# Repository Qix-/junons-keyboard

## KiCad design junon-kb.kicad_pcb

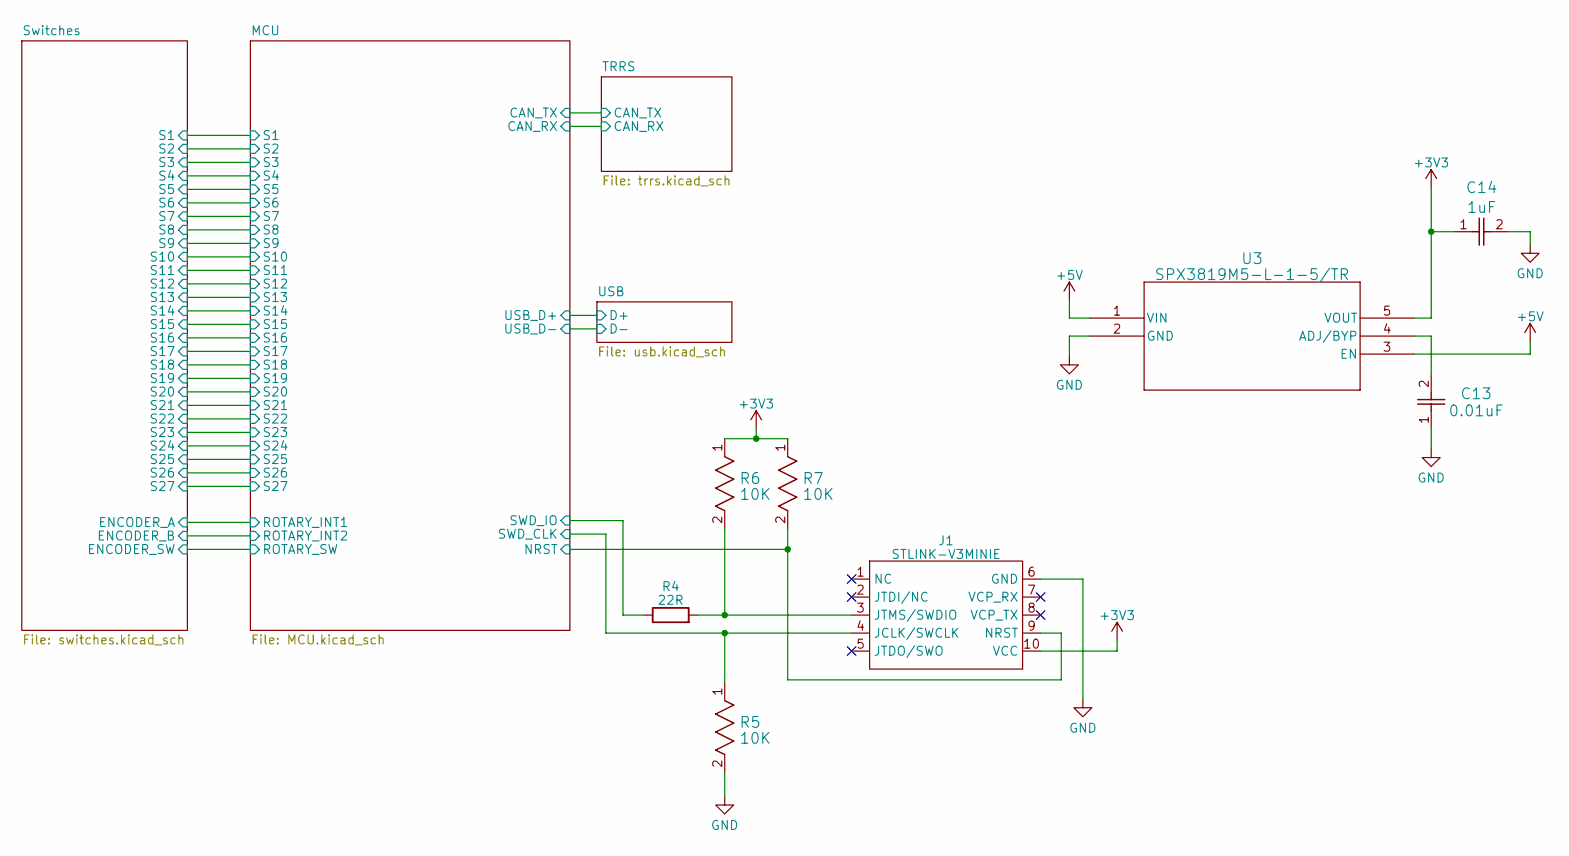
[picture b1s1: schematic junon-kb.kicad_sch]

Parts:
C13: 0.01uF; CAP_CL21_SAM; DigiKey ID 1276-1015-1-ND
C14: 1uF; CAP_0603G_AVX; Mouser ID 581-0603YD105K
J1: STLINK-V3MINIE; 009159010061911; Manufacturer_Part_Number STLINK-V3MINIE; Mouser Part Number 511-STLINK-V3MINIE
R4: 22R; R_01005_0402Metric
R5, R6, R7: 10K; RES_RK73H1E_KOA; Mouser ID 660-RK73H1ETTP1002F
U3: SPX3819M5-L-1-5/TR; SOT-23-5_VAR-AA; Mouser ID 701-SPX3819M5-L-15TR

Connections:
+3V3: C14.1, J1.10 (VCC), R6.1, R7.1, U3.5 (VOUT); also elsewhere on the board
+5V: U3.1 (VIN), U3.3 (EN); also elsewhere on the board
/MCU/NRST: J1.9 (NRST), R7.2; also elsewhere on the board
/MCU/SWD_CLK: J1.4 (JCLK/SWCLK), R5.1; also elsewhere on the board
/MCU/SWD_IO: R4.1; also elsewhere on the board
GND: C13.1, C14.2, J1.6 (GND), R5.2, U3.2 (GND); also elsewhere on the board
unnamed: J1.3 (JTMS/SWDIO), R4.2, R6.2
unnamed: C13.2, U3.4 (ADJ/BYP)

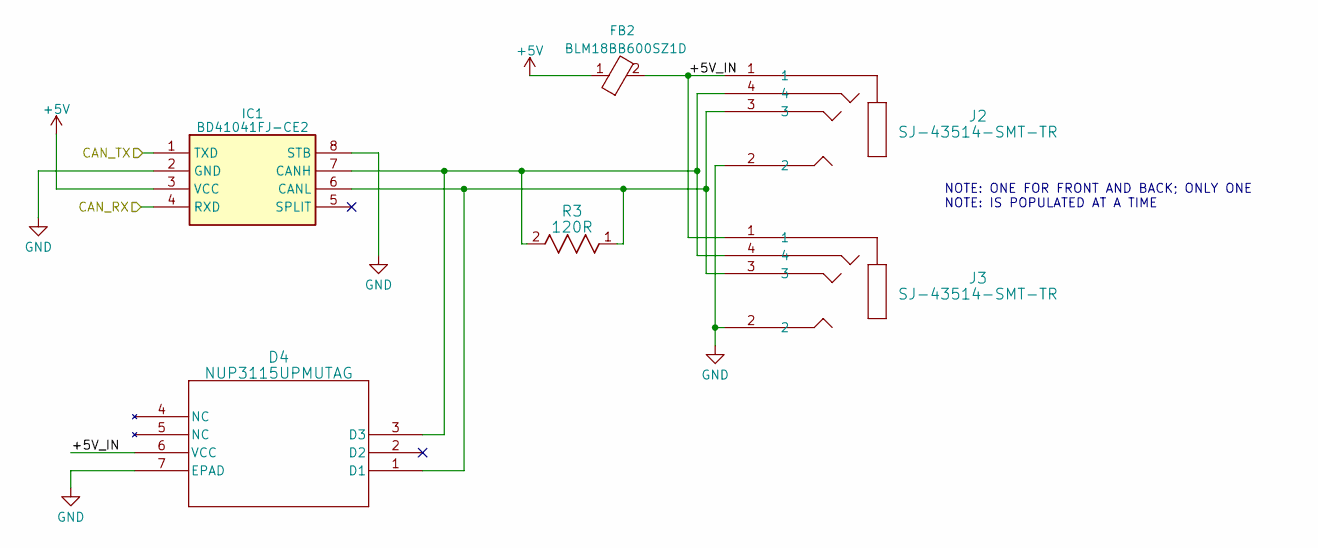
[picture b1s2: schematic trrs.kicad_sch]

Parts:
D4: NUP3115UPMUTAG; UDFN6_1P60X1P60_ONS; Mouser ID 863-NUP3115UPMUTAG
FB2: BLM18BB600SZ1D; BLM18EG121SH1D; Manufacturer_Part_Number BLM18BB600SZ1D; Mouser Part Number 81-BLM18BB600SZ1D
IC1: BD41041FJ-CE2; SOIC127P600X165-8N; Manufacturer_Part_Number BD41041FJ-CE2; Mouser Part Number 755-BD41041FJ-CE2
J2, J3: SJ-43514-SMT-TR; SJ-43514-SMT_CUD; DigiKey ID CP-43514SJCT-ND
R3: 120R; RES_0603_1P6XP8_PAN; Mouser ID 667-ERJ-PA3F1200V

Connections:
+5V: FB2.1, IC1.3 (VCC); also elsewhere on the board
/MCU/CAN_RX: IC1.4 (RXD); also elsewhere on the board
/MCU/CAN_TX: IC1.1 (TXD); also elsewhere on the board
/TRRS/+5V_IN: D4.6 (VCC), FB2.2, J2.1, J3.1
GND: D4.7 (EPAD), IC1.2 (GND), IC1.8 (STB), J2.2, J3.2; also elsewhere on the board
unnamed: D4.1 (D1), IC1.6 (CANL), J2.3, J3.3, R3.1
unnamed: D4.3 (D3), IC1.7 (CANH), J2.4, J3.4, R3.2

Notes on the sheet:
NOTE: ONE FOR FRONT AND BACK; ONLY ONE NOTE: IS POPULATED AT A TIME

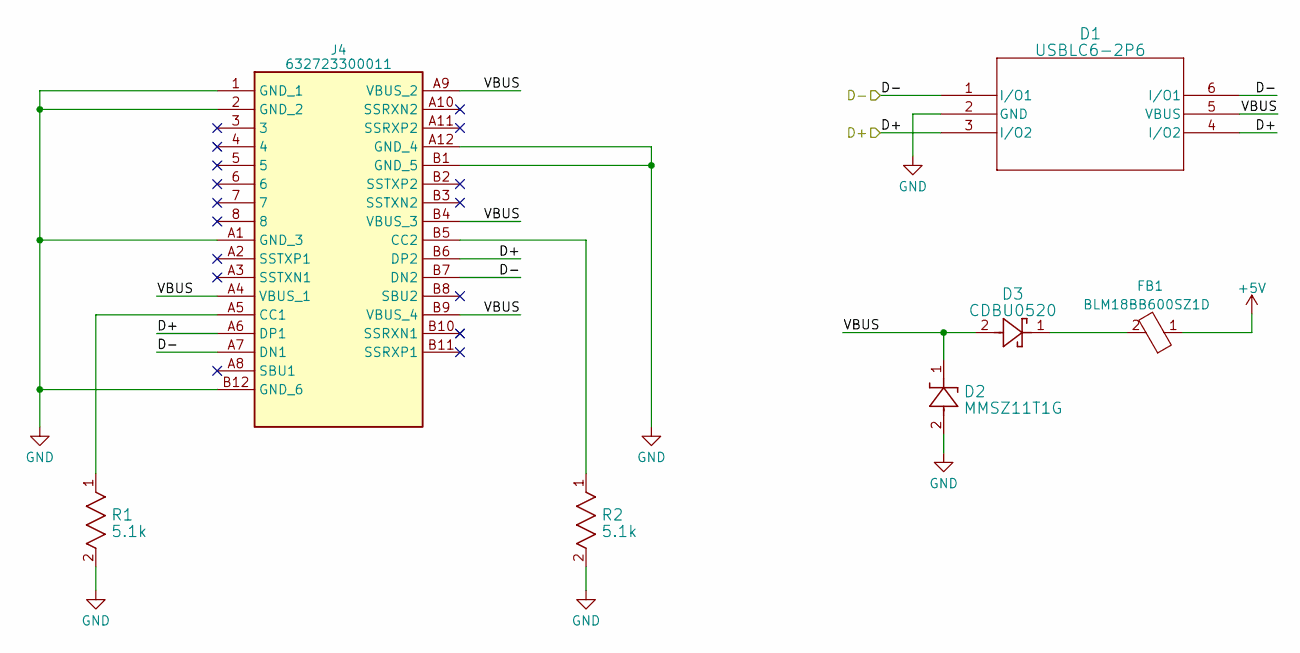
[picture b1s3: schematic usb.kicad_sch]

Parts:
D1: USBLC6-2P6; SOT-666_STM; Mouser ID 511-USBLC6-2P6
D2: MMSZ11T1G; SOD-123_ONS; Mouser ID 863-MMSZ11T1G
D3: CDBU0520; CDBU; Mouser ID 750-CDBU0520
FB1: BLM18BB600SZ1D; BLM18EG121SH1D; Manufacturer_Part_Number BLM18BB600SZ1D; Mouser Part Number 81-BLM18BB600SZ1D
J4: 632723300011; Manufacturer_Part_Number 632723300011; Mouser Part Number 710-632723300011
R1, R2: 5.1k; RES_ERJUP3_PAN; Mouser ID 667-ERJ-UP3F5101V

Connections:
+5V: FB1.1; also elsewhere on the board
/USB/D+: D1.3 (I/O2), D1.4 (I/O2), J4.A6 (DP1), J4.B6 (DP2); also elsewhere on the board
/USB/D-: D1.1 (I/O1), D1.6 (I/O1), J4.A7 (DN1), J4.B7 (DN2); also elsewhere on the board
/USB/VBUS: D1.5 (VBUS), D2.1, D3.2, J4.A4 (VBUS_1), J4.A9 (VBUS_2), J4.B4 (VBUS_3), J4.B9 (VBUS_4)
GND: D1.2 (GND), D2.2, J4.1 (GND_1), J4.2 (GND_2), J4.A1 (GND_3), J4.A12 (GND_4), J4.B1 (GND_5), J4.B12 (GND_6), R1.2, R2.2; also elsewhere on the board
unnamed: D3.1, FB1.2
unnamed: J4.A5 (CC1), R1.1
unnamed: J4.B5 (CC2), R2.1

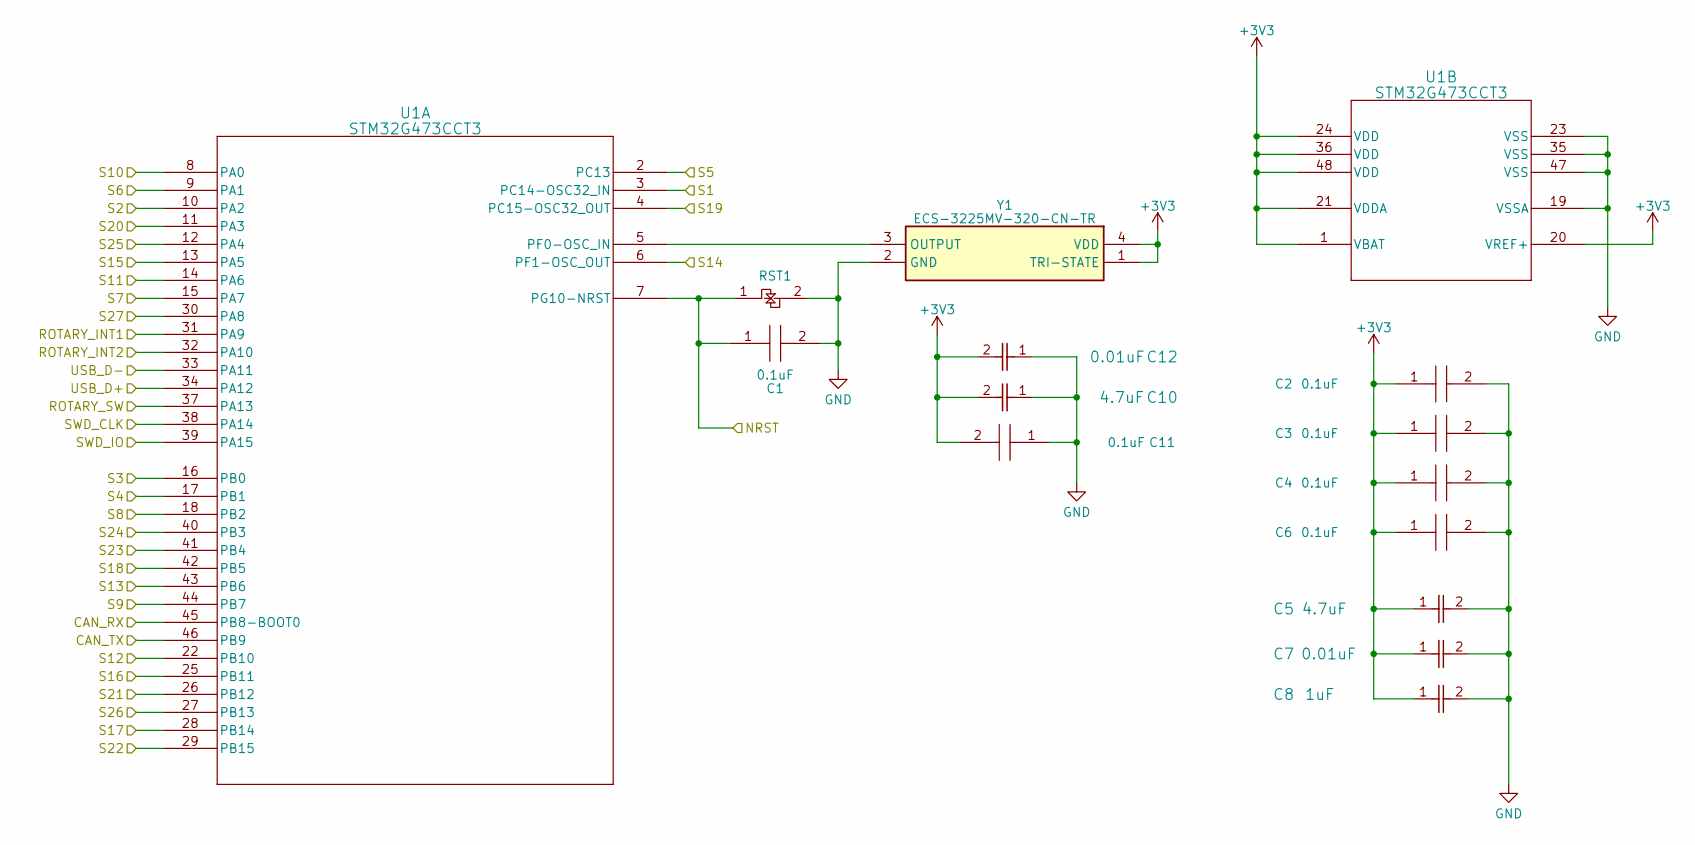
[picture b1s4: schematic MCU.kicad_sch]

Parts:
C1, C2, C3, C4, C6, C11: 0.1uF; CAPC1005X33N; Manufacturer_Part_Number MSAST1L3YB5104KFNA01; Mouser Part Number 963-MSAST1L3YB5104KF
C5, C10: 4.7uF; CAP_CL21_SAM; Mouser URL null
C7, C12: 0.01uF; CAP_CL21_SAM; DigiKey ID 1276-1015-1-ND
C8: 1uF; CAP_0603G_AVX; Mouser ID 581-0603YD105K
RST1: RESET-2P-EDGE
U1: STM32G473CCT3; LQFP48-7x7mm; Mouser ID 511-STM32G473CCT3
Y1: ECS-3225MV-320-CN-TR; ECS3225MV320BNTR; Manufacturer_Part_Number ECS-3225MV-320-CN-TR; Mouser Part Number 520-3225MV-320-CNT

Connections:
+3V3: C2.1, C3.1, C4.1, C5.1, C6.1, C7.1, C8.1, C10.2, C11.2, C12.2, U1.1 (VBAT), U1.20 (VREF+), U1.21 (VDDA), U1.24 (VDD), U1.36 (VDD), U1.48 (VDD), Y1.1 (TRI-STATE), Y1.4 (VDD); also elsewhere on the board
/MCU/CAN_RX: U1.45 (PB8-BOOT0); also elsewhere on the board
/MCU/CAN_TX: U1.46 (PB9); also elsewhere on the board
/MCU/NRST: C1.1, RST1.1, U1.7 (PG10-NRST); also elsewhere on the board
/MCU/ROTARY_INT1: U1.31 (PA9); also elsewhere on the board
/MCU/ROTARY_INT2: U1.32 (PA10); also elsewhere on the board
/MCU/ROTARY_SW: U1.37 (PA13); also elsewhere on the board
/MCU/S1: U1.3 (PC14-OSC32_IN); also elsewhere on the board
/MCU/S2: U1.10 (PA2); also elsewhere on the board
/MCU/S3: U1.16 (PB0); also elsewhere on the board
/MCU/S4: U1.17 (PB1); also elsewhere on the board
/MCU/S5: U1.2 (PC13); also elsewhere on the board
/MCU/S6: U1.9 (PA1); also elsewhere on the board
/MCU/S7: U1.15 (PA7); also elsewhere on the board
/MCU/S8: U1.18 (PB2); also elsewhere on the board
/MCU/S9: U1.44 (PB7); also elsewhere on the board
/MCU/S10: U1.8 (PA0); also elsewhere on the board
/MCU/S11: U1.14 (PA6); also elsewhere on the board
/MCU/S12: U1.22 (PB10); also elsewhere on the board
/MCU/S13: U1.43 (PB6); also elsewhere on the board
/MCU/S14: U1.6 (PF1-OSC_OUT); also elsewhere on the board
/MCU/S15: U1.13 (PA5); also elsewhere on the board
/MCU/S16: U1.25 (PB11); also elsewhere on the board
/MCU/S17: U1.28 (PB14); also elsewhere on the board
/MCU/S18: U1.42 (PB5); also elsewhere on the board
/MCU/S19: U1.4 (PC15-OSC32_OUT); also elsewhere on the board
/MCU/S20: U1.11 (PA3); also elsewhere on the board
/MCU/S21: U1.26 (PB12); also elsewhere on the board
/MCU/S22: U1.29 (PB15); also elsewhere on the board
/MCU/S23: U1.41 (PB4); also elsewhere on the board
/MCU/S24: U1.40 (PB3); also elsewhere on the board
/MCU/S25: U1.12 (PA4); also elsewhere on the board
/MCU/S26: U1.27 (PB13); also elsewhere on the board
/MCU/S27: U1.30 (PA8); also elsewhere on the board
/MCU/SWD_CLK: U1.38 (PA14); also elsewhere on the board
/MCU/SWD_IO: U1.39 (PA15); also elsewhere on the board
/USB/D+: U1.34 (PA12); also elsewhere on the board
/USB/D-: U1.33 (PA11); also elsewhere on the board
GND: C1.2, C2.2, C3.2, C4.2, C5.2, C6.2, C7.2, C8.2, C10.1, C11.1, C12.1, RST1.2, U1.19 (VSSA), U1.23 (VSS), U1.35 (VSS), U1.47 (VSS), Y1.2 (GND); also elsewhere on the board
unnamed: U1.5 (PF0-OSC_IN), Y1.3 (OUTPUT)

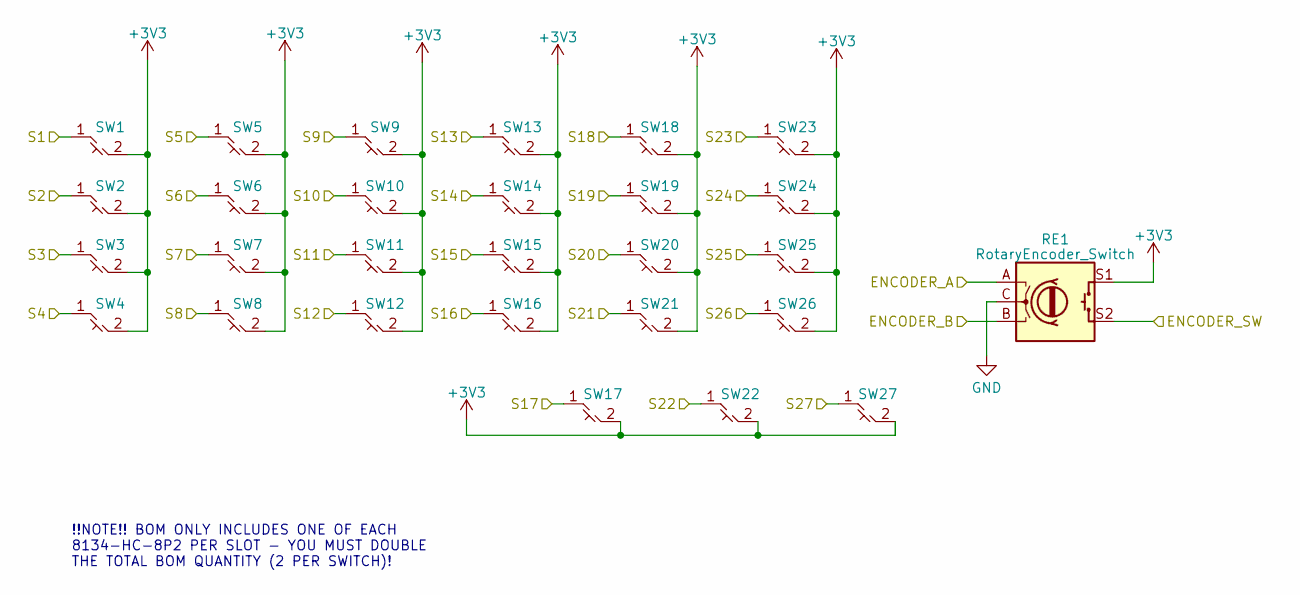
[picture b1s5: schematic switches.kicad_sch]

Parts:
RE1: RotaryEncoder_Switch; RotaryEncoder_Alps_EC11E-Switch_Vertical_H20mm
SW1, SW2, SW3, SW4, SW5, SW6, SW7, SW8, SW9, SW10, SW11, SW12, SW13, SW14, SW15, SW16, SW17, SW18, SW19, SW20, SW21, SW22, SW23, SW24, SW25, SW26, SW27: SW_Cherry_MX_1.00u_PCB

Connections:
+3V3: RE1.S1, SW1.2, SW2.2, SW3.2, SW4.2, SW5.2, SW6.2, SW7.2, SW8.2, SW9.2, SW10.2, SW11.2, SW12.2, SW13.2, SW14.2, SW15.2, SW16.2, SW17.2, SW18.2, SW19.2, SW20.2, SW21.2, SW22.2, SW23.2, SW24.2, SW25.2, SW26.2, SW27.2; also elsewhere on the board
/MCU/ROTARY_INT1: RE1.A; also elsewhere on the board
/MCU/ROTARY_INT2: RE1.B; also elsewhere on the board
/MCU/ROTARY_SW: RE1.S2; also elsewhere on the board
/MCU/S1: SW1.1; also elsewhere on the board
/MCU/S2: SW2.1; also elsewhere on the board
/MCU/S3: SW3.1; also elsewhere on the board
/MCU/S4: SW4.1; also elsewhere on the board
/MCU/S5: SW5.1; also elsewhere on the board
/MCU/S7: SW7.1; also elsewhere on the board
/MCU/S8: SW8.1; also elsewhere on the board
/MCU/S9: SW9.1; also elsewhere on the board
/MCU/S10: SW10.1; also elsewhere on the board
/MCU/S11: SW11.1; also elsewhere on the board
/MCU/S13: SW13.1; also elsewhere on the board
/MCU/S14: SW14.1; also elsewhere on the board
/MCU/S15: SW15.1; also elsewhere on the board
/MCU/S16: SW16.1; also elsewhere on the board
/MCU/S17: SW17.1; also elsewhere on the board
/MCU/S19: SW19.1; also elsewhere on the board
/MCU/S20: SW20.1; also elsewhere on the board
/MCU/S21: SW21.1; also elsewhere on the board
/MCU/S22: SW22.1; also elsewhere on the board
/MCU/S23: SW23.1; also elsewhere on the board
/MCU/S25: SW25.1; also elsewhere on the board
/MCU/S26: SW26.1; also elsewhere on the board
/MCU/S27: SW27.1; also elsewhere on the board
GND: RE1.C; also elsewhere on the board

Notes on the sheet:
!!NOTE!! BOM ONLY INCLUDES ONE OF EACH 8134-HC-8P2 PER SLOT - YOU MUST DOUBLE THE TOTAL BOM QUANTITY (2 PER SWITCH)!

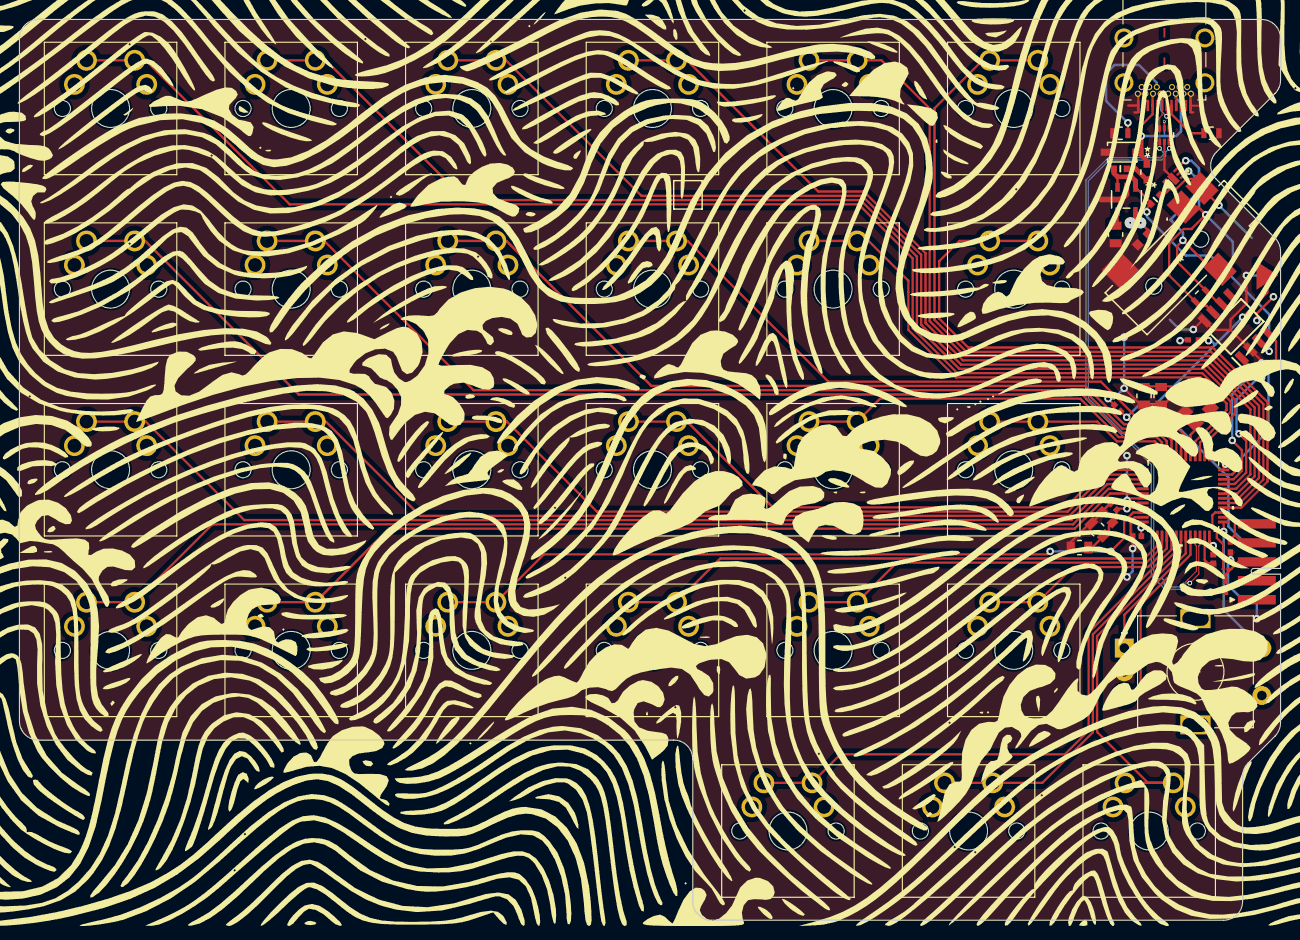
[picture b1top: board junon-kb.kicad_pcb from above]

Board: 2 copper layers, 133.0 x 95.0 mm, 63 parts (1 on the bottom side), 50 nets.

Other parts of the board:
locked: locked; SW_Cherry_MX_1.00u_PCB
locked#2, locked#3, locked#4: locked; SW_Cherry_MX_1.00u_PCB

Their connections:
+3V3: locked.2, locked#2.2, locked#3.2, locked#4.2; also elsewhere on the board
/MCU/S6: locked#3.1; also elsewhere on the board
/MCU/S12: locked#4.1; also elsewhere on the board
/MCU/S18: locked.1; also elsewhere on the board
/MCU/S24: locked#2.1; also elsewhere on the board

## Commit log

2024-01-20 more artifacts
2024-01-20 add bootstrapped firmware
2024-01-26 fix typo in firmware.run phony
2024-02-08 update NRST
2024-02-08 flesh out SWD circuit
2024-03-06 next version
